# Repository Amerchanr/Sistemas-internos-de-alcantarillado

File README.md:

# Sistemas de Internos de alcantarillado
## Descripción del Problema
Dentro de complejos empresariales y residenciales, los sistemas internos de alcantarillado están diseñados para recolectar las aguas residuales y dirigirlas hacia el sistema principal de la ciudad. Estos sistemas suelen emplear bombas trituradoras para extraer el agua, pero debido a la falta de conciencia social, las personas tienden a desechar residuos de gran tamaño en las alcantarillas, lo que provoca obstrucciones frecuentes. La acumulación de sólidos en las aguas residuales genera graves consecuencias técnicas, económicas y sociales. Las obstrucciones deterioran rápidamente las bombas, aumentan los costos de mantenimiento y reparaciones, y originan reboses que causan contaminación ambiental, malos olores y afectan la calidad de vida de las comunidades cercanas.

En lugares críticos como centros comerciales, estos problemas impactan negativamente la actividad económica al alejar a los clientes. Además, las intervenciones correctivas realizadas por los técnicos deben ejecutarse en entornos peligrosos, húmedos y contaminados, lo que conlleva altos riesgos laborales. Por lo tanto, es necesario implementar un sistema de control que prevenga los daños recurrentes en las bombas y otros componentes del sistema de alcantarillado, asegurando su correcto funcionamiento, prolongando su vida útil y minimizando los riesgos asociados.

## Descripción del Prototipo
Para abordar esta problemática, se propone desarrollar un prototipo basado en
sensores y tecnologías IoT, diseñado para monitorear y detectar taponamientos de
manera temprana en tiempo real. Este sistema permitirá identificar condiciones
críticas, como acumulación de sólidos o cambios en la presión, y enviará alertas a
los técnicos encargados antes de que ocurran fallas mayores. Además, el prototipo
facilitará el mantenimiento preventivo, optimizando recursos, minimizando los daños
en las bombas y prolongando su vida útil. Este enfoque también busca garantizar la
seguridad de los técnicos y reducir los impactos negativos en la comunidad,
promoviendo un modelo sostenible y replicable para sistemas de bombeo similares.

## Requerimientos
### Requerimientos funcionales de Hardware

- Se requiere de sensor que me permita obtener información sobre el nivel del agua
- Se requiere un sensor que permita medir el flujo que la bomba está enviando a través de la tubería
- Se requiere de una protección física que evite que la bomba se vea afectada por atascamientos.
- Se requiere de un sistema de respaldo que verifique el correcto funcionamiento de los sensores

### Requerimientos no funcionales de Hardware

- El sistema debe ser capaz de ampliarse para integrar másnsensores o actuadores sin necesidad de rediseñar su arquitectura.
- El sistema debe operar de forma continua y garantizar un tiempo de inactividad no mayor al 1% durante su operación anual.
- Los componentes del sistema deben ser eficientes en términos de energía, reduciendo el impacto ambiental y los costos operativos.

### Requerimientos funcionales de Software
- Se requiereque el sistema permita visualizar variables críticas, como nivel y flujo en tiempo real desde la interfaz HMI. 
- Se requiere que la interfaz de usuario envíe una alerta visual y auditiva al dispositivo del técnico, para notificar cualquier cambio o problema en el estado de las bombas.
- Se requiere un sistema de control sea capaz de almacenar la información proporcionada por los sensores y en función de esos datos, activar o desactivar la bomba.
- Se requiere que el software almacene los datos registrados durante  un rango de 6 meses ,permitiendo la generación de reportes y análisis.
- 
### Requerimientos no funcionales de Software
- El sistema debe contar con protocolos de encriptación y autenticación de usuarios para proteger los datos y prevenir accesos no autorizados.

## Diagrama de Flujo

## Diagrama de Caja Negra

## Diagrama Tecnologico

### Para Mayor Información revisar el siguiente documento pdf
[Ver documento PDF](./docunmentacion.pdf)

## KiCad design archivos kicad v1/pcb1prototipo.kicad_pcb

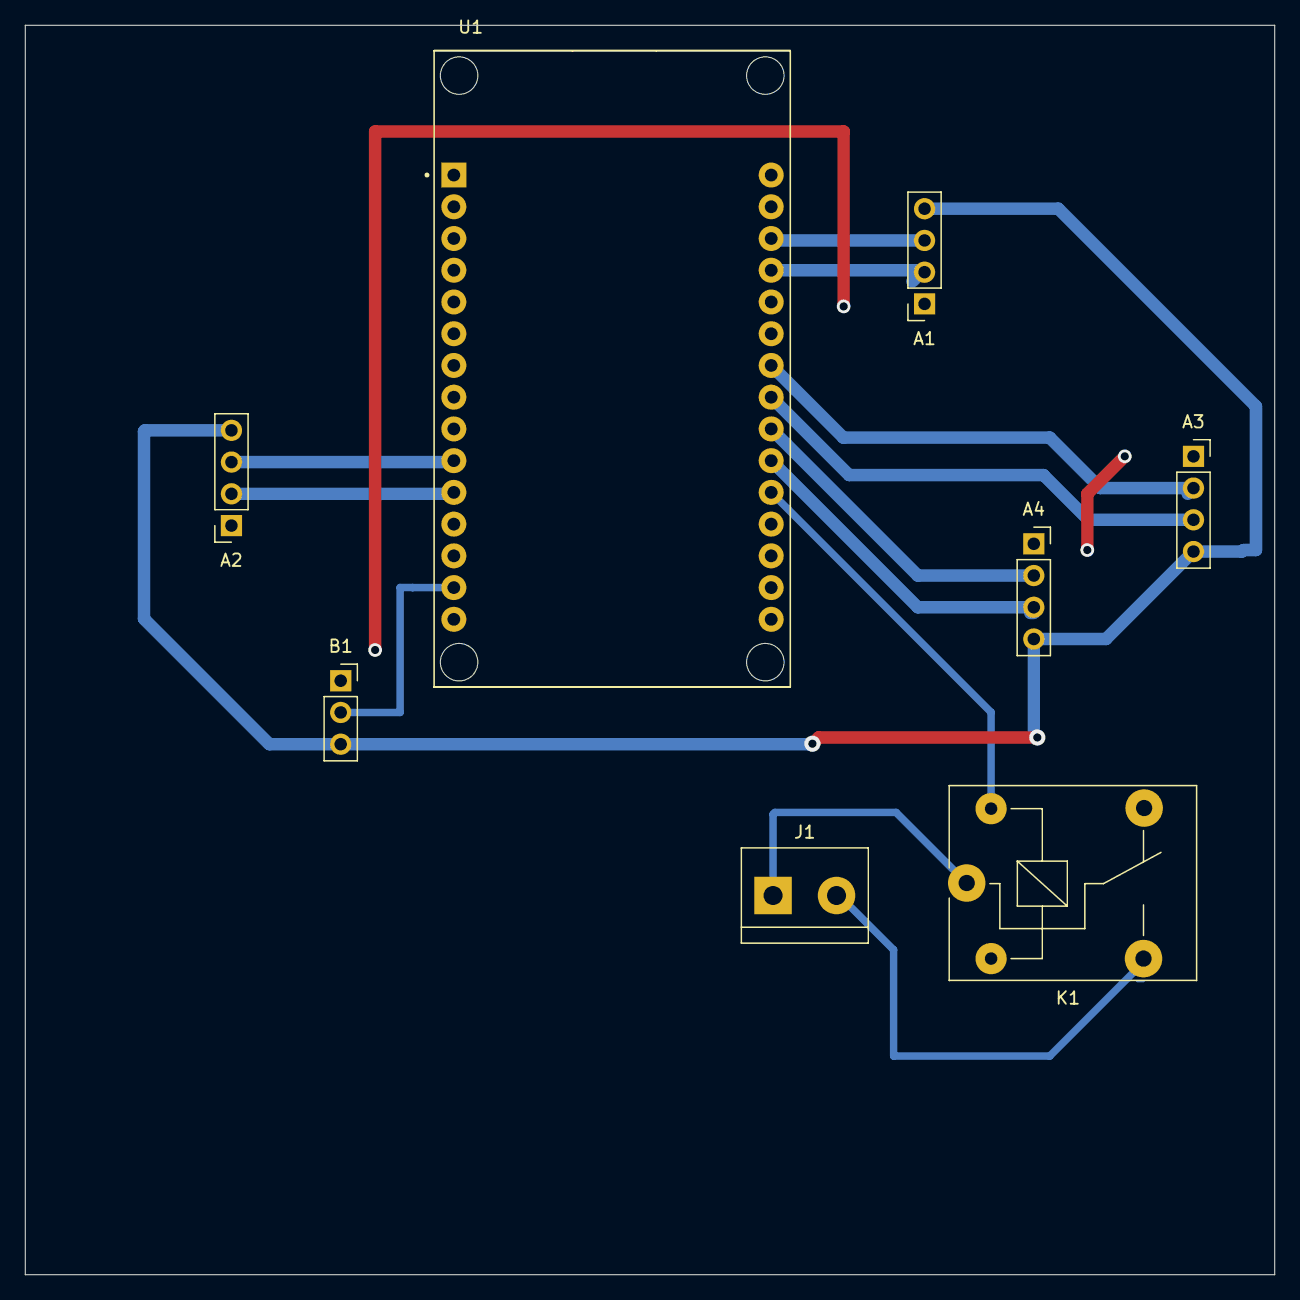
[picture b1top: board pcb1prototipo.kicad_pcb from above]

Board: 2 copper layers, 100.0 x 100.0 mm, 8 parts (0 on the bottom side), 14 nets.

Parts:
A1, A2, A3, A4: Ultrasonido; PinSocket_1x04_P2.54mm_Vertical
B1: DHT-11; PinSocket_1x03_P2.54mm_Vertical
J1: BORN2PINS; TerminalBlock_bornier-2_P5.08mm
K1: RELAY; Relay_SPDT_SANYOU_SRD_Series_Form_C
U1: ESP32-DEVKIT-V1; MODULE_ESP32_DEVKIT_V1

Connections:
+5V: A1.4, A2.4, A3.4, A4.4, B1.3
/DHT: B1.2, U1.14 (D22)
/ECHO1: A1.2, U1.27 (D12)
/ECHO2: A2.2, U1.11 (D21)
/ECHO3: A3.2, U1.24 (D26)
/ECHO4: A4.2, U1.22 (D33)
/RELatSp: K1.5, U1.20 (D35)
/TRIGER1: A1.3, U1.28 (D13)
/TRIGER2: A2.3, U1.10 (D19)
/TRIGER3: A3.3, U1.23 (D25)
/TRIGER4: A4.3, U1.21 (D32)
GND: A1.1, A2.1, A3.1, A4.1, B1.1
unnamed: J1.1, K1.1
unnamed: J1.2, K1.3

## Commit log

2025-01-22 commit 22/01/1.1
2025-01-22 commit 22/01/1.2
2025-01-22 commit 22/01/1.3
2025-01-22 commit 22/01/1.4
2025-01-24 commit 24/01/1.1
2025-01-27 commit 27/01/1.1
2025-01-28 commit 27/01/1.2
2025-03-08 Archivos gerber para impresion de PCB
